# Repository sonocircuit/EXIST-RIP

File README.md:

# EXI[S]T: an adaption of Mannequins' RIP module.

Mannequins RIP module by Whimsical Raps is now [open source](https://github.com/whimsicalraps/RIP_DIY). EXI[S]T is an adaption thereof and can be configured in several ways. The name is a tribute to Meng Qi's module "Please Exist".

## Modes of use

The main PCB – *the transformer board* – is meant to be mounted inside the case. The inputs and outputs can be connected in serveral ways. Any configuration of the listed options below is possible.

**Input option A:** <br> The inputs are conncted to the *transformer board* via 16 pin ribbon cable from the 1u EXI[S]T module. The 1u modules are available in Intellijel (12HP) and Pulplogic (10HP) format and house the input jacks, lift switch and an attenuating volume pot. <br>

**Input option B:** <br> An [Intelligel Mixup](https://intellijel.com/shop/eurorack/mixup) module can be connceted directly to the *transformer board* via the molex 3pin output bus connector. This configuration makes the 1u module redundant and ground lift may be engaged directly on the transformer board with two jumpers.

**Output option A:** <br> TRS Jacks can be connected to the *transformer board* with wires via the "TRS" pads. <br>

**Output option B:** <br> The 6pin header can be connected either to an Intellijel [Audio Jack rev2 board](https://intellijel.com/shop/cases/7u-audio-jacks-board-v2) or an Intellijel [Stereo Line Out Jacks module](https://intellijel.com/shop/eurorack/1u/stereo-line-out-jacks-1u) via 6 pin ribbon cable.

## Make you own

**PCBs:** All [eagle files](https://github.com/sonoCircuits/EXIST-RIP/tree/master/EXIST-EAGLE%20FILES) can be found in the repro in case you wish to have PCB's fabricated.

**BOM:** Here is the [OCTOPART BOM](https://octopart.com/bom-tool/6HVkKHyi). Please note that the silkscreen of the mixup header on the *transformer board* should be rotated by 180° (rotate the header before soldering, otherwise L and R channels will be swapped). The silkscreen has been corrected on the Eagle files.

## Credits

Thanks to [Whimsical Raps](http://whimsicalraps.com) for designing RIP and making the files open source, and to Meng Qi for the name inspiration.

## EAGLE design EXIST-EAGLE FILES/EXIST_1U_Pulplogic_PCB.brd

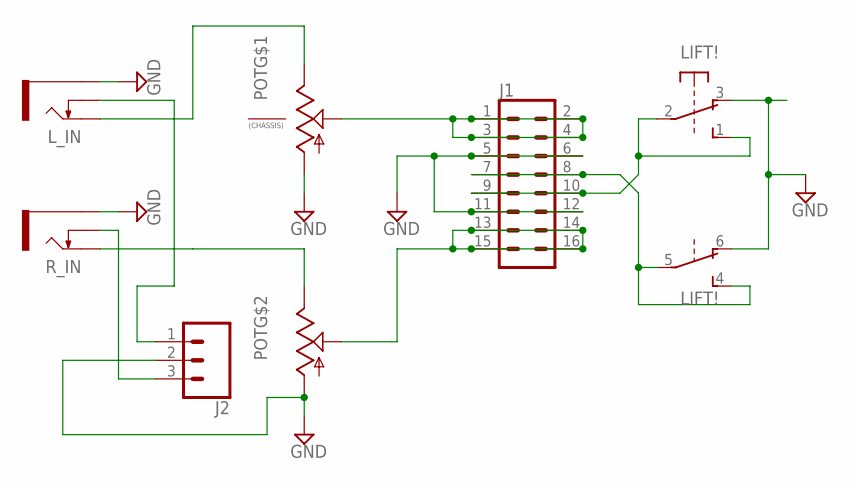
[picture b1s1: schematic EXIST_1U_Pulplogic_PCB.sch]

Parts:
J1: CONN_08X2; 2X8
J2: CONN_03; 1X03
LIFT!: 9450-2
L_IN: THONKICONNNEW; WQP-PJ301M-12_JACK
POT: ALPHA-9MM-DUALPOT; DUAL_9MM_SNAP-IN_POT
R_IN: THONKICONNNEW; WQP-PJ301M-12_JACK

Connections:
GND: J1.5, J1.6, J1.11, J1.12, J2.2, LIFT!.3 (O), LIFT!.6 (O), L_IN.P$3_SLEEVE (SLEEVE), POT.1 (A), POT.1B (A), R_IN.P$3_SLEEVE (SLEEVE)
unnamed: J1.13, J1.14, J1.15, J1.16, POT.2B (S)
unnamed: J1.1, J1.2, J1.3, J1.4, POT.2 (S)
unnamed: J1.7, J1.8, LIFT!.4 (S), LIFT!.5
unnamed: J2.1, L_IN.P$2_SWITCH (SWITCH)
unnamed: POT.3B (E), R_IN.P$1_TIP (TIP)
unnamed: L_IN.P$1_TIP (TIP), POT.3 (E)
unnamed: J2.3, R_IN.P$2_SWITCH (SWITCH)
unnamed: J1.9, J1.10, LIFT!.1 (S), LIFT!.2

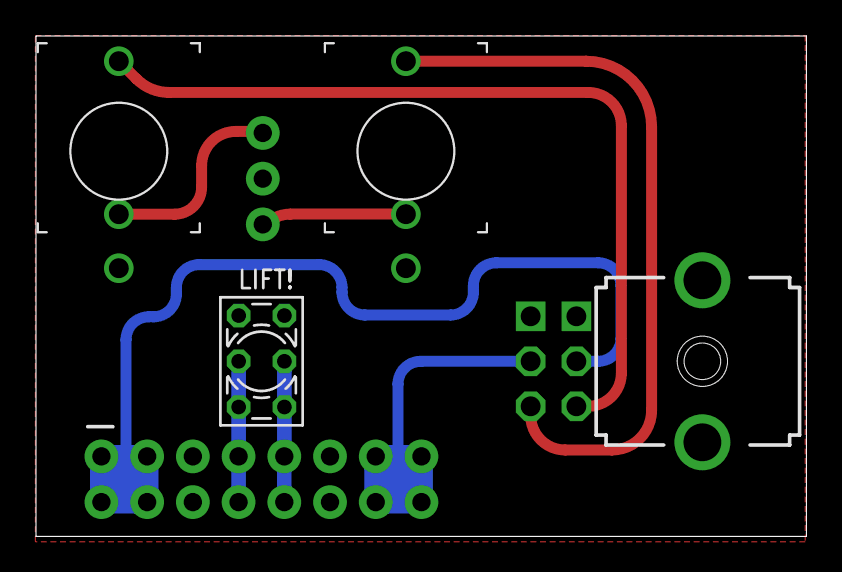
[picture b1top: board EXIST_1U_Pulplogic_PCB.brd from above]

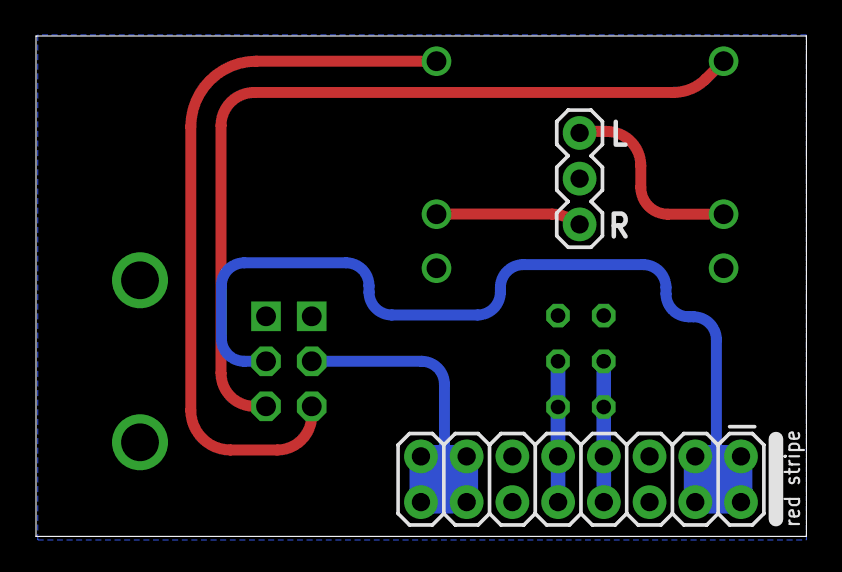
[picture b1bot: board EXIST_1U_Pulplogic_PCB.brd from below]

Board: 2 copper layers, 42.8 x 27.8 mm, 6 parts (2 on the bottom side), 9 nets.

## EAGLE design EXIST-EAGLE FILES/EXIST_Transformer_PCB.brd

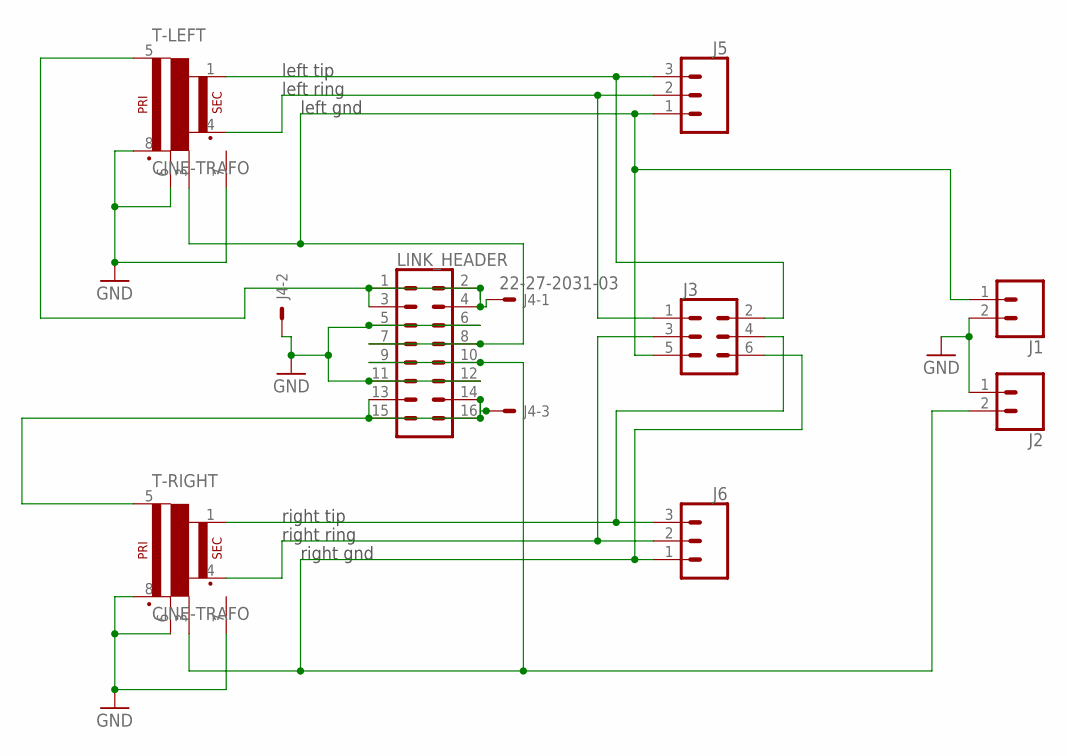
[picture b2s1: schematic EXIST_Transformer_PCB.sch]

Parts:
J1, J2: CONN_02; 1X02
J3: CONN_03X22X3_SILK_MALE_PTH; 2X3
J4: 22-27-2031-03; 6410-03
J5, J6: CONN_03LONGPADS; 1X03_LONGPADS
LINK_HEADER: CONN_08X2; 2X8
T-LEFT: CINE-TRAFO; CIRC-TRAFO
T-RIGHT: CINE-TRAFO; CIRC-TRAFO

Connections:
GND: J1.2, J2.1, J4.2, LINK_HEADER.5, LINK_HEADER.6, LINK_HEADER.11, LINK_HEADER.12, T-LEFT.6 (C1), T-LEFT.7 (CASE), T-LEFT.8 (P2), T-RIGHT.6 (C1), T-RIGHT.7 (CASE), T-RIGHT.8 (P2)
LEFT-GND: J1.1, J3.5, J5.1, LINK_HEADER.7, LINK_HEADER.8, T-LEFT.3 (C2)
LEFT-RING: J3.1, J5.2, T-LEFT.4 (S2)
unnamed: J3.2, J5.3, T-LEFT.1 (S1)
unnamed: J3.4, J6.3, T-RIGHT.1 (S1)
unnamed: J3.3, J6.2, T-RIGHT.4 (S2)
unnamed: J4.3, LINK_HEADER.13, LINK_HEADER.14, LINK_HEADER.15, LINK_HEADER.16, T-RIGHT.5 (P1)
unnamed: J4.1, LINK_HEADER.1, LINK_HEADER.2, LINK_HEADER.3, LINK_HEADER.4, T-LEFT.5 (P1)
RIGHT-GND: J2.2, J3.6, J6.1, LINK_HEADER.9, LINK_HEADER.10, T-RIGHT.3 (C2)

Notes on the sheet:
left tip
left ring
left gnd
right tip
right ring
right gnd

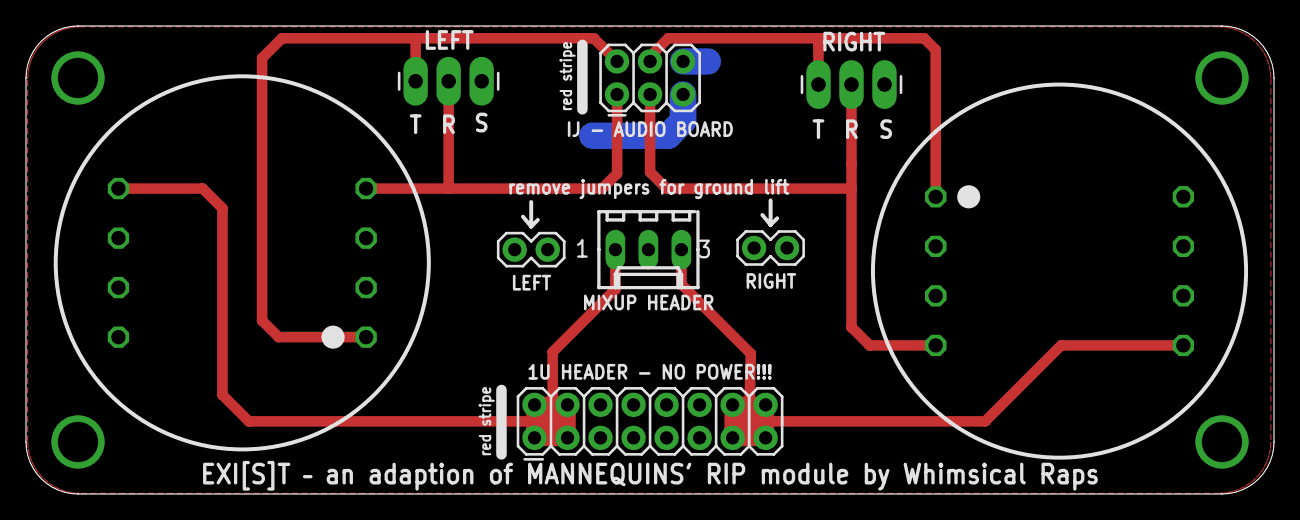
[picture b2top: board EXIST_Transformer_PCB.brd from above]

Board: 2 copper layers, 96.0 x 36.0 mm, 9 parts (0 on the bottom side), 9 nets.

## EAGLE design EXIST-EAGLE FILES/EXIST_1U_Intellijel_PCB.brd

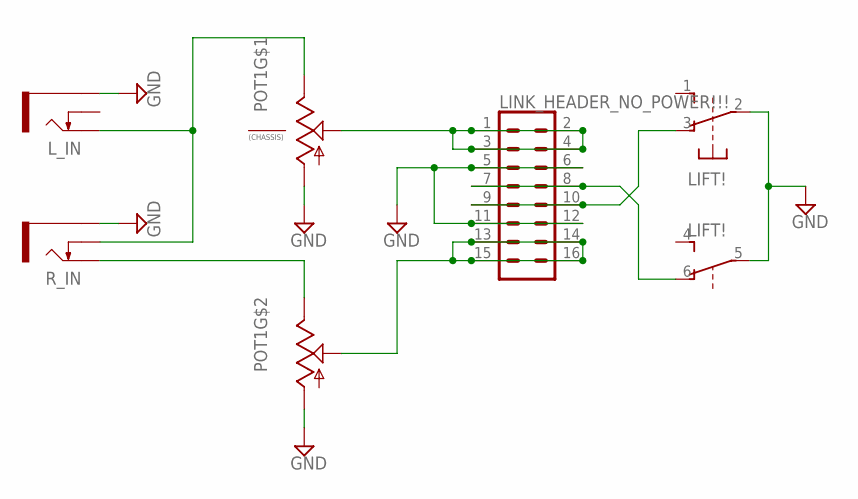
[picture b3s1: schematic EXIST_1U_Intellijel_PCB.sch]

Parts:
LIFT!: 9450-2
LINK_HEADER_NO_POWER!!!: CONN_08X2; 2X8
L_IN: THONKICONNNEW; WQP-PJ301M-12_JACK
POT1: ALPHA-9MM-DUALPOT; DUAL_9MM_SNAP-IN_POT
R_IN: THONKICONNNEW; WQP-PJ301M-12_JACK

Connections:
GND: LIFT!.2, LIFT!.5, LINK_HEADER_NO_POWER!!!.5, LINK_HEADER_NO_POWER!!!.6, LINK_HEADER_NO_POWER!!!.11, LINK_HEADER_NO_POWER!!!.12, L_IN.P$3_SLEEVE (SLEEVE), POT1.1 (A), POT1.1B (A), R_IN.P$3_SLEEVE (SLEEVE)
unnamed: LINK_HEADER_NO_POWER!!!.13, LINK_HEADER_NO_POWER!!!.14, LINK_HEADER_NO_POWER!!!.15, LINK_HEADER_NO_POWER!!!.16, POT1.2B (S)
unnamed: LINK_HEADER_NO_POWER!!!.1, LINK_HEADER_NO_POWER!!!.2, LINK_HEADER_NO_POWER!!!.3, LINK_HEADER_NO_POWER!!!.4, POT1.2 (S)
unnamed: LIFT!.6 (O), LINK_HEADER_NO_POWER!!!.7, LINK_HEADER_NO_POWER!!!.8
unnamed: LIFT!.3 (O), LINK_HEADER_NO_POWER!!!.9, LINK_HEADER_NO_POWER!!!.10
unnamed: POT1.3B (E), R_IN.P$1_TIP (TIP)
unnamed: L_IN.P$1_TIP (TIP), POT1.3 (E), R_IN.P$2_SWITCH (SWITCH)

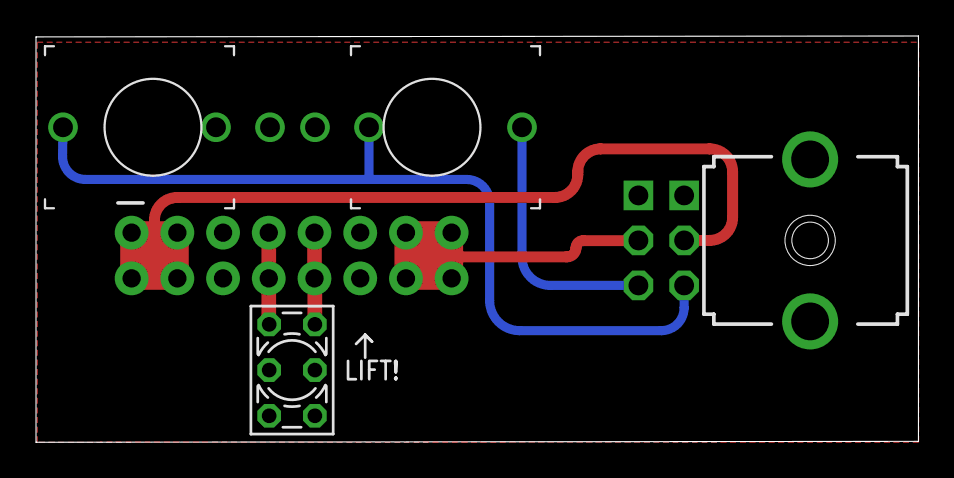
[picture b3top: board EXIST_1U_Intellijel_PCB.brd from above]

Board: 2 copper layers, 49.0 x 22.6 mm, 5 parts (1 on the bottom side), 7 nets.

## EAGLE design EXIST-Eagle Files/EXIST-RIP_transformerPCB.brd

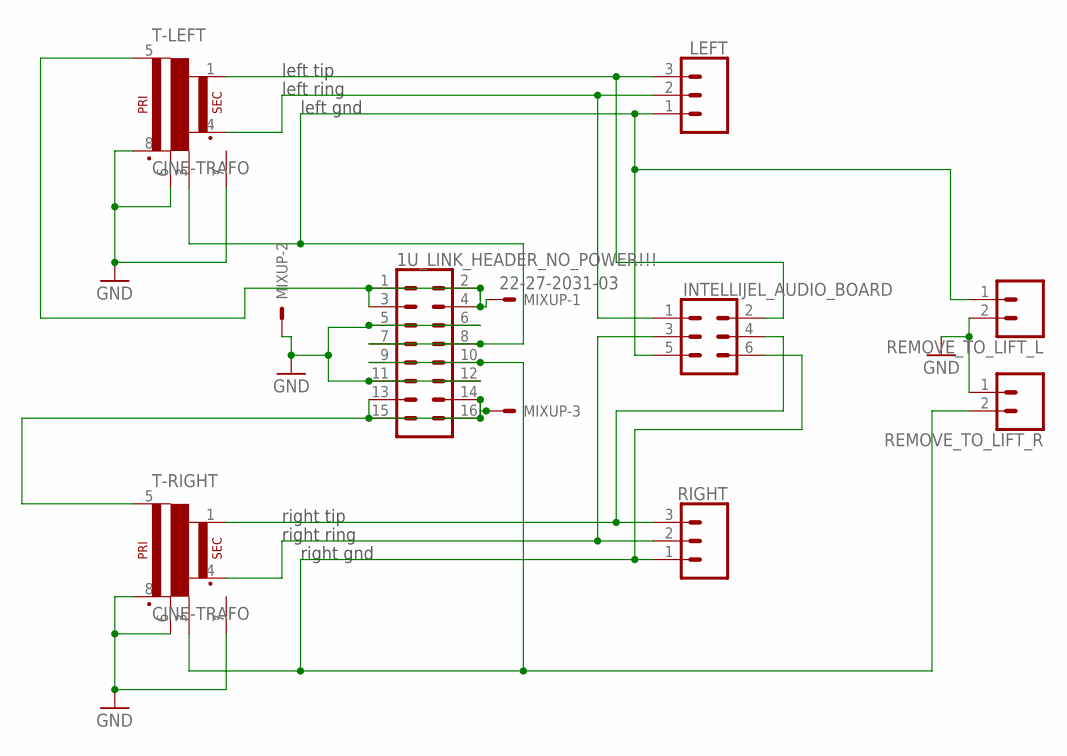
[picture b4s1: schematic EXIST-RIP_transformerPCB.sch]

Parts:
1U_LINK_HEADER_NO_POWER!!!: CONN_08X2; 2X8
INTELLIJEL_AUDIO_BOARD: CONN_03X22X3_SILK_MALE_PTH; 2X3
LEFT: CONN_03LONGPADS; 1X03_LONGPADS
MIXUP: 22-27-2031-03; 6410-03
REMOVE_TO_LIFT_L: CONN_02; 1X02
REMOVE_TO_LIFT_R: CONN_02; 1X02
RIGHT: CONN_03LONGPADS; 1X03_LONGPADS
T-LEFT: CINE-TRAFO; CIRC-TRAFO
T-RIGHT: CINE-TRAFO; CIRC-TRAFO

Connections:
GND: 1U_LINK_HEADER_NO_POWER!!!.5, 1U_LINK_HEADER_NO_POWER!!!.6, 1U_LINK_HEADER_NO_POWER!!!.11, 1U_LINK_HEADER_NO_POWER!!!.12, MIXUP.2, REMOVE_TO_LIFT_L.2, REMOVE_TO_LIFT_R.1, T-LEFT.6 (C1), T-LEFT.7 (CASE), T-LEFT.8 (P2), T-RIGHT.6 (C1), T-RIGHT.7 (CASE), T-RIGHT.8 (P2)
LEFT-GND: 1U_LINK_HEADER_NO_POWER!!!.7, 1U_LINK_HEADER_NO_POWER!!!.8, INTELLIJEL_AUDIO_BOARD.5, LEFT.1, REMOVE_TO_LIFT_L.1, T-LEFT.3 (C2)
LEFT-RING: INTELLIJEL_AUDIO_BOARD.1, LEFT.2, T-LEFT.4 (S2)
unnamed: INTELLIJEL_AUDIO_BOARD.2, LEFT.3, T-LEFT.1 (S1)
unnamed: INTELLIJEL_AUDIO_BOARD.4, RIGHT.3, T-RIGHT.1 (S1)
unnamed: INTELLIJEL_AUDIO_BOARD.3, RIGHT.2, T-RIGHT.4 (S2)
unnamed: 1U_LINK_HEADER_NO_POWER!!!.13, 1U_LINK_HEADER_NO_POWER!!!.14, 1U_LINK_HEADER_NO_POWER!!!.15, 1U_LINK_HEADER_NO_POWER!!!.16, MIXUP.3, T-RIGHT.5 (P1)
unnamed: 1U_LINK_HEADER_NO_POWER!!!.1, 1U_LINK_HEADER_NO_POWER!!!.2, 1U_LINK_HEADER_NO_POWER!!!.3, 1U_LINK_HEADER_NO_POWER!!!.4, MIXUP.1, T-LEFT.5 (P1)
RIGHT-GND: 1U_LINK_HEADER_NO_POWER!!!.9, 1U_LINK_HEADER_NO_POWER!!!.10, INTELLIJEL_AUDIO_BOARD.6, REMOVE_TO_LIFT_R.2, RIGHT.1, T-RIGHT.3 (C2)

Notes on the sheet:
left tip
left ring
left gnd
right tip
right ring
right gnd

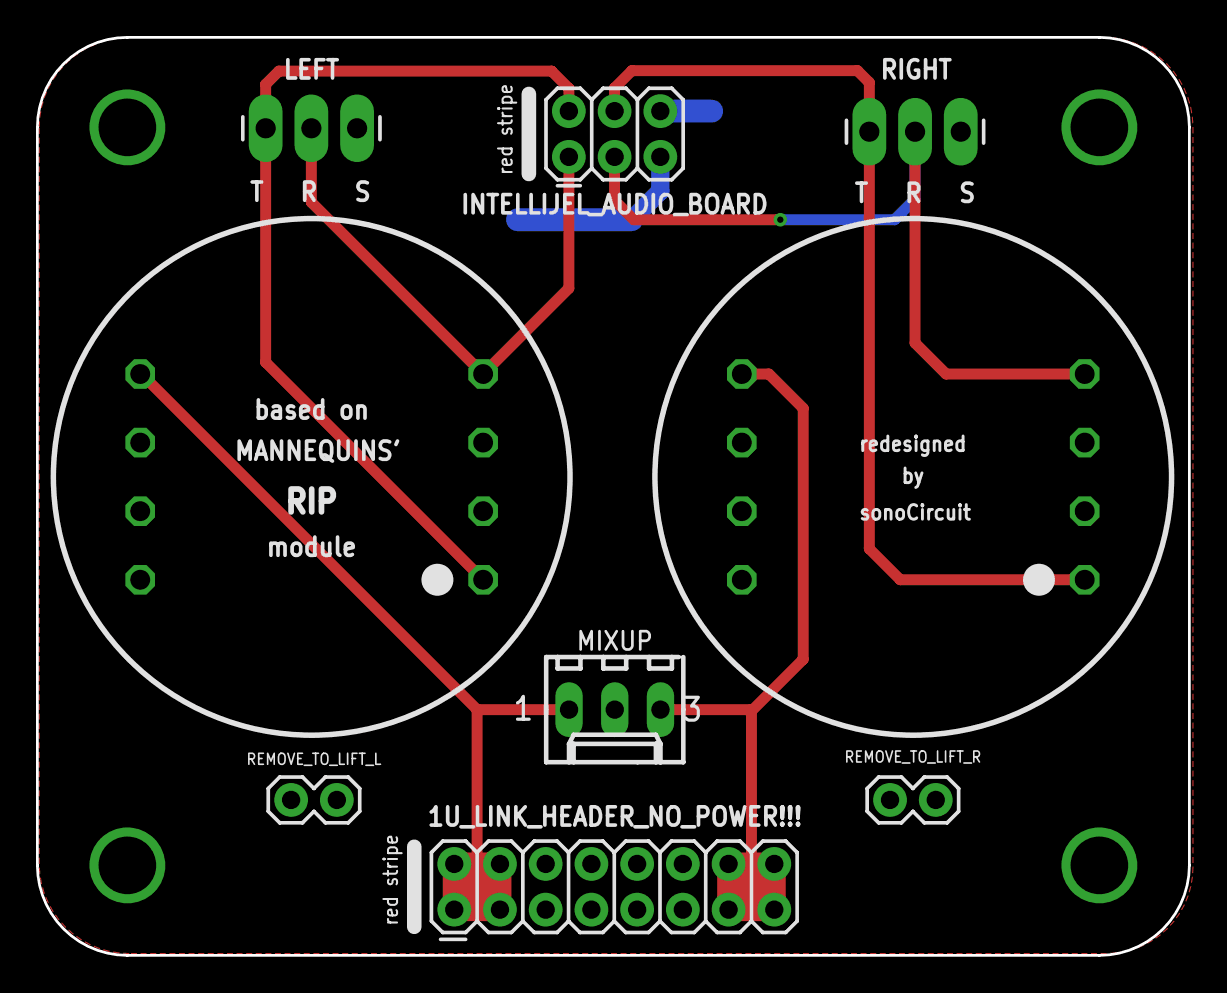
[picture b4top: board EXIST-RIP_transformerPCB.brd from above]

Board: 2 copper layers, 64.0 x 51.0 mm, 9 parts (0 on the bottom side), 9 nets.

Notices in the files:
parts and their libraries:
SparkFun-Connectors: Licensing: Creative Commons ShareAlike 4.0 International - https://creativecommons.org/licenses/by-sa/4.0
